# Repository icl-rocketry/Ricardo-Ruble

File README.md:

# Ricardo-Ruble
Mini Buck-Boost Converter

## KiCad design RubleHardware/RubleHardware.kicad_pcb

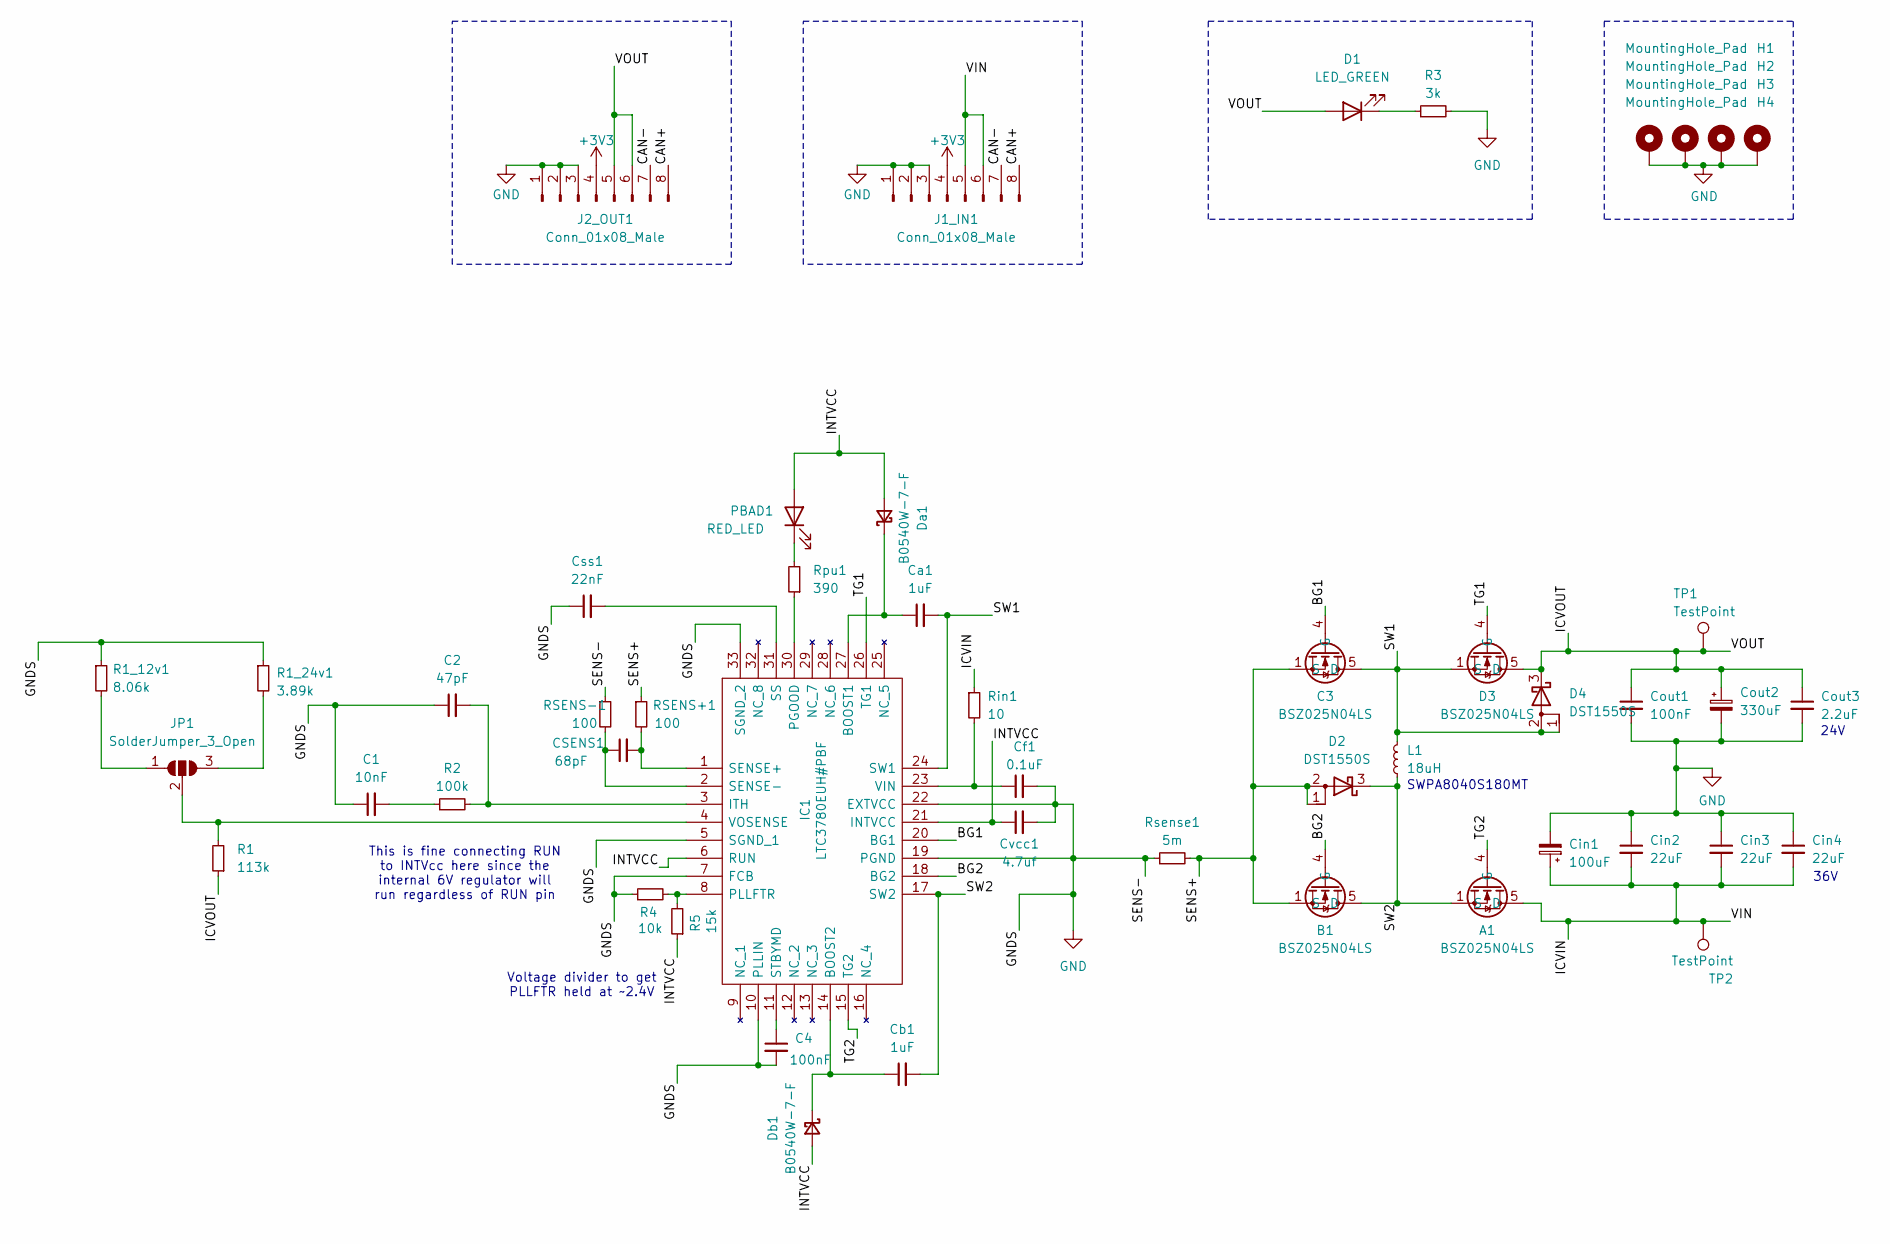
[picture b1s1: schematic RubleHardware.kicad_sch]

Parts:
A1: BSZ025N04LS; Manufacturer_Part_Number BSZ025N04LS; Mouser Part Number 726-BSZ025N04LS
B1: BSZ025N04LS; Manufacturer_Part_Number BSZ025N04LS; Mouser Part Number 726-BSZ025N04LS
C1: 10nF; C_0402_1005Metric
C2: 47pF; C_0402_1005Metric
C3: BSZ025N04LS; Manufacturer_Part_Number BSZ025N04LS; Mouser Part Number 726-BSZ025N04LS
C4: 100nF; C_0603_1608Metric
CSENS1: 68pF; C_0402_1005Metric
Ca1: 1uF; C_0402_1005Metric
Cb1: 1uF; C_0402_1005Metric
Cf1: 0.1uF; C_0402_1005Metric
Cin1: 100uF; CP_EIA-7360-38_Kemet-E
Cin2, Cin3, Cin4: 22uF; CAPC2012X145N
Cout1: 100nF; CAPC1608X90N
Cout2: 330uF; CAPAE1030X1050N
Cout3: 2.2uF; RESC2013X65N
Css1: 22nF; C_0402_1005Metric
Cvcc1: 4.7uf; C_0402_1005Metric
D1: LED_GREEN; LED_0402_1005Metric
D2, D4: DST1550S; TO-277B
D3: BSZ025N04LS; Manufacturer_Part_Number BSZ025N04LS; Mouser Part Number 726-BSZ025N04LS
Da1: B0540W-7-F; SODFL3516X70N
Db1: B0540W-7-F; SODFL3516X70N
H1, H2, H3, H4: MountingHole_Pad; MountingHole_3.2mm_M3_DIN965_Pad
IC1: LTC3780EUH#PBF; QFN-32_UH; Mouser Part Number 584-LTC3780EUH#PBF
J1_IN1, J2_OUT1: Conn_01x08_Male; Molex_Mini-Fit_Jr_5569-08A2_2x04_P4.20mm_Horizontal
JP1: SolderJumper_3_Open; SolderJumper-3_P2.0mm_Open_TrianglePad1.0x1.5mm
L1: 18uH; L_Sunlord_SWPA8040S
PBAD1: RED_LED; LED_0402_1005Metric
R1: 113k; R_0402_1005Metric_Pad0.72x0.64mm_HandSolder
R1_12v1: 8.06k; R_0402_1005Metric_Pad0.72x0.64mm_HandSolder
R1_24v1: 3.89k; RESC2013X65N
R2: 100k; R_0402_1005Metric_Pad0.72x0.64mm_HandSolder
R3: 3k; R_0402_1005Metric
R4: 10k; R_0402_1005Metric
R5: 15k; R_0402_1005Metric
RSENS+1: 100; R_0402_1005Metric_Pad0.72x0.64mm_HandSolder
RSENS-1: 100; R_0402_1005Metric_Pad0.72x0.64mm_HandSolder
Rin1: 10; R_0402_1005Metric_Pad0.72x0.64mm_HandSolder
Rpu1: 390; R_0402_1005Metric_Pad0.72x0.64mm_HandSolder
Rsense1: 5m; RESC6432X67N
TP1, TP2: TestPoint; TestPoint_Pad_D1.5mm

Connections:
+3V3: J1_IN1.4, J2_OUT1.4
/BG1: C3.4 (G), IC1.20 (BG1)
/BG2: B1.4 (G), IC1.18 (BG2)
/CAN+: J1_IN1.8, J2_OUT1.8
/CAN-: J1_IN1.7, J2_OUT1.7
/ICVIN: A1.5 (D), A1.6 (D), A1.7 (D), A1.8 (D), A1.A5 (D), Cin1.1, Cin2.2, Cin3.2, Cin4.2, J1_IN1.5, J1_IN1.6, Rin1.1, TP2.1
/ICVOUT: Cout1.1, Cout2.1, Cout3.1, D1.2 (A), D3.5 (D), D3.6 (D), D3.7 (D), D3.8 (D), D3.A5 (D), D4.3 (K), J2_OUT1.5, J2_OUT1.6, R1.1, TP1.1
/INTVCC: Cvcc1.1, Da1.2 (A), Db1.2 (A), IC1.6 (RUN), IC1.21 (INTVCC), PBAD1.2 (A), R5.1
/SENS+: B1.1 (S), B1.2 (S), B1.3 (S), B1.A1 (S), C3.1 (S), C3.2 (S), C3.3 (S), C3.A1 (S), D2.1 (A), D2.2 (A), RSENS+1.1, Rsense1.2
/SW1: C3.5 (D), C3.6 (D), C3.7 (D), C3.8 (D), C3.A5 (D), Ca1.2, D3.1 (S), D3.2 (S), D3.3 (S), D3.A1 (S), D4.1 (A), D4.2 (A), IC1.24 (SW1), L1.2
/SW2: A1.1 (S), A1.2 (S), A1.3 (S), A1.A1 (S), B1.5 (D), B1.6 (D), B1.7 (D), B1.8 (D), B1.A5 (D), Cb1.2, D2.3 (K), IC1.17 (SW2), L1.1
/TG1: D3.4 (G), IC1.26 (TG1)
/TG2: A1.4 (G), IC1.15 (TG2)
GND: C1.1, C2.1, C4.2, Cf1.2, Cin1.2, Cin2.1, Cin3.1, Cin4.1, Cout1.2, Cout2.2, Cout3.2, Css1.1, Cvcc1.2, H1.1, H2.1, H3.1, H4.1, IC1.5 (SGND_1), IC1.7 (FCB), IC1.10 (PLLIN), IC1.19 (PGND), IC1.22 (EXTVCC), IC1.33 (SGND_2), J1_IN1.1, J1_IN1.2, J1_IN1.3, J2_OUT1.1, J2_OUT1.2, J2_OUT1.3, R1_12v1.1, R1_24v1.1, R3.2, R4.1, RSENS-1.1, Rsense1.1
unnamed: C1.2, R2.1
unnamed: D1.1 (K), R3.1
unnamed: Ca1.1, Da1.1 (K), IC1.27 (BOOST1)
unnamed: Cb1.1, Db1.1 (K), IC1.14 (BOOST2)
unnamed: C2.2, IC1.3 (ITH), R2.2
unnamed: IC1.30 (PGOOD), Rpu1.1
unnamed: IC1.8 (PLLFTR), R4.2, R5.2
unnamed: CSENS1.2, IC1.1 (SENSE+), RSENS+1.2
unnamed: CSENS1.1, IC1.2 (SENSE-), RSENS-1.2
unnamed: Css1.2, IC1.31 (SS)
unnamed: C4.1, IC1.11 (STBYMD)
unnamed: Cf1.1, IC1.23 (VIN), Rin1.2
unnamed: IC1.4 (VOSENSE), JP1.2 (C), R1.2
unnamed: JP1.1 (A), R1_12v1.2
unnamed: JP1.3 (B), R1_24v1.2
unnamed: PBAD1.1 (K), Rpu1.2

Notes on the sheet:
SWPA8040S180MT
This is fine connecting RUN to INTVcc here since the internal 6V regulator will run regardless of RUN pin
Voltage divider to get PLLFTR held at ~2.4V
24V
36V

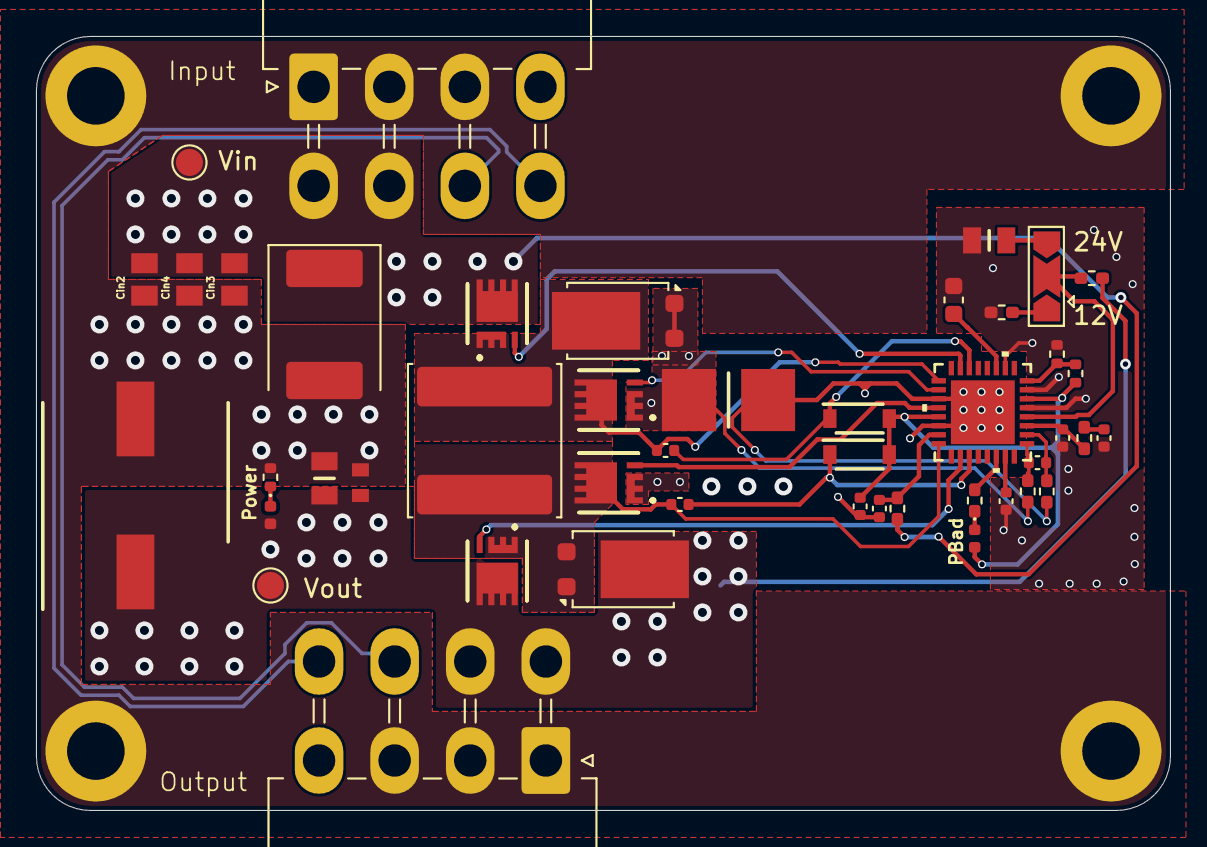
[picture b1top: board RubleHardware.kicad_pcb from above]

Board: 4 copper layers, 63.0 x 43.0 mm, 49 parts (0 on the bottom side), 30 nets.

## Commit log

2025-03-13 feat: Adding in values to board
2025-03-22 feat: First review feedback
2025-03-22 feat: Pulled up enable pin
2025-04-04 feat: Changes almost complete for feedbak
2025-04-04 feat: Update vout and vin caps
2025-04-04 feat: Stopped being stupid and connected grounds
2025-05-20 mega commit ;)
2025-05-21 feat: First board revision
2025-06-11 feat: Board V2
2025-06-21 feat: V2.0 changes to schematic
2025-06-24 feat: v3 almost complete
2025-06-24 feat: V0.3 ready
2025-08-04 feat: First stage of changes
2025-08-04 trying something out
2025-08-04 feat: Redesign completer
2025-08-11 feat: v0.4 ready
2025-08-20 Minor tweaks
    Moved GND mounting holes away from edge
